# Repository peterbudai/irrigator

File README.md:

# IrriGator

WiFi enabled irrigation control

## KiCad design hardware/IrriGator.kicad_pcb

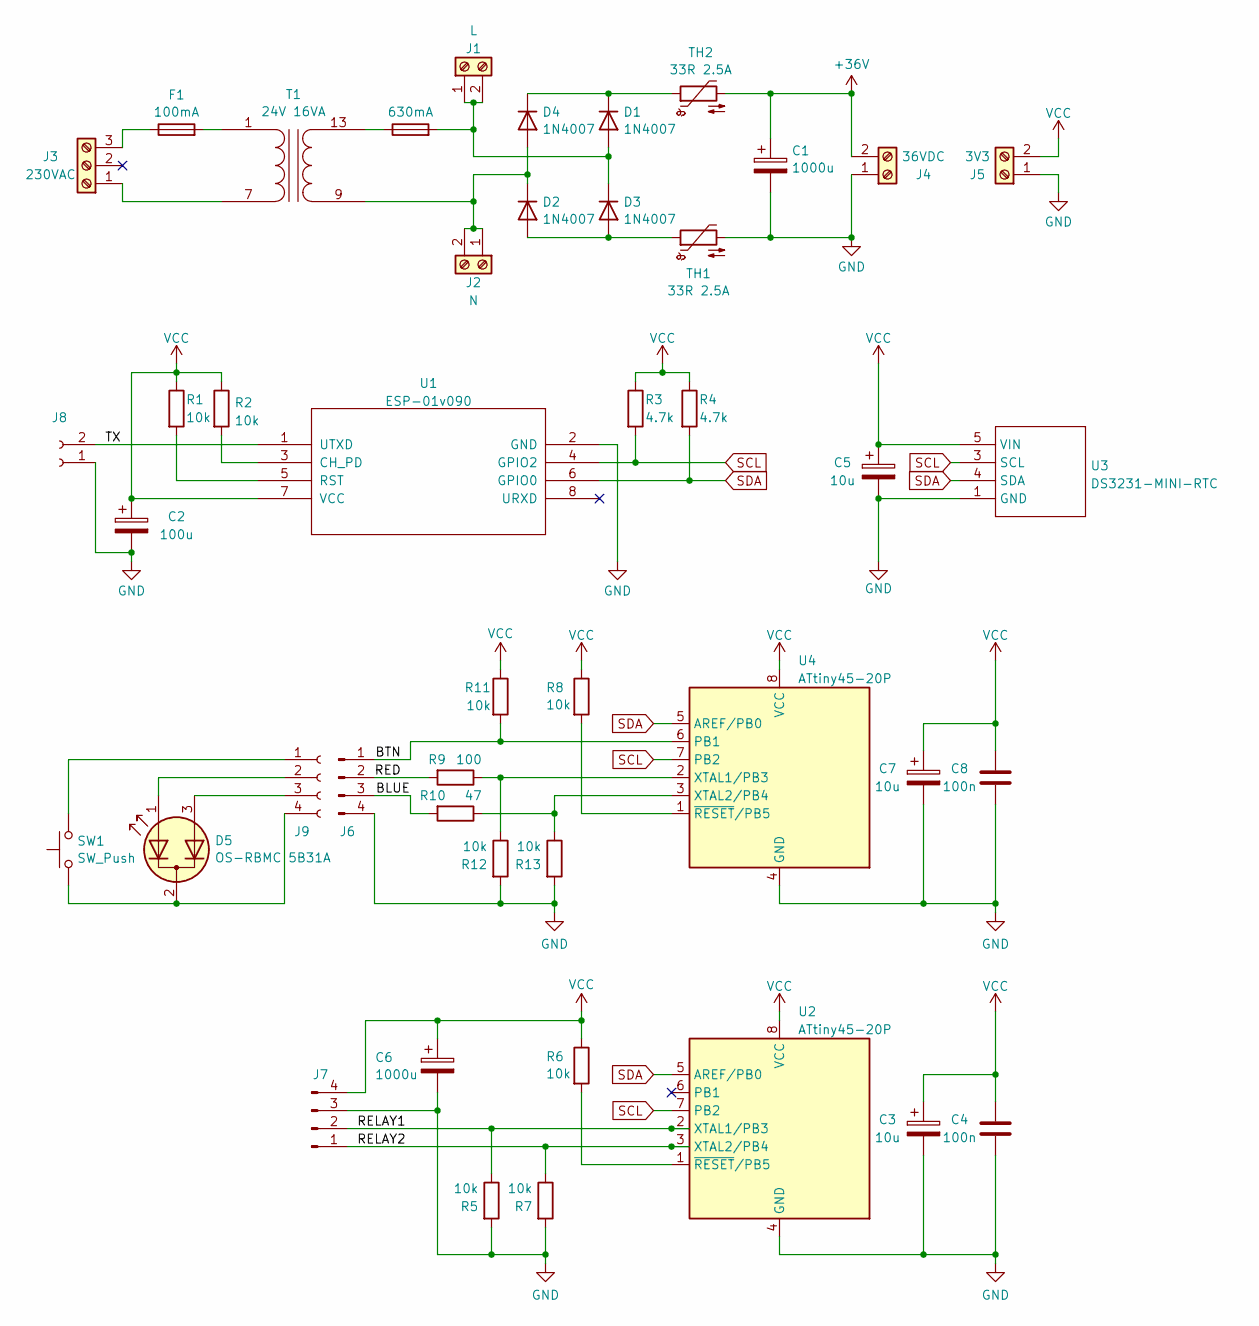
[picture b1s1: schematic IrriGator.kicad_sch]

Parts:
C1: 1000u; CP_Radial_D16.0mm_P7.50mm
C2: 100u; CP_Radial_D5.0mm_P2.50mm
C3, C5, C7: 10u; CP_Radial_D5.0mm_P2.50mm
C4, C8: 100n; C_Disc_D5.0mm_W2.5mm_P2.50mm
C6: 1000u; CP_Radial_D10.0mm_P5.00mm
D1, D2, D3, D4: 1N4007; D_DO-41_SOD81_P10.16mm_Horizontal
D5: OS-RBMC 5B31A; LED_D5.0mm-3
F1: 100mA; Fuseholder_Cylinder-5x20mm_Stelvio-Kontek_PTF78_Horizontal_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
F2: 630mA; Fuseholder_Cylinder-5x20mm_Stelvio-Kontek_PTF78_Horizontal_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
J1: L; TerminalBlock_Phoenix_MKDS-1,5-2-5.08_1x02_P5.08mm_Horizont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
J2: N; TerminalBlock_Phoenix_MKDS-1,5-2-5.08_1x02_P5.08mm_Horizont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
J3: 230VAC; TerminalBlock_Phoenix_MKDS-1,5-3-5.08_1x03_P5.08mm_Horizont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
J4: 36VDC; TerminalBlock_Phoenix_MKDS-1,5-2-5.08_1x02_P5.08mm_Horizont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
J5: 3V3; TerminalBlock_Phoenix_MKDS-1,5-2-5.08_1x02_P5.08mm_Horizont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
J6, J7: Conn_01x04_Pin; PinHeader_1x04_P2.54mm_Vertical
J8: Conn_01x02_Socket; PinSocket_1x02_P2.54mm_Vertical
J9: Conn_01x04_Socket; SolderWire-0.1sqmm_1x04_P3.6mm_D0.4mm_OD1mm
R1, R2, R5, R6, R7, R8, R11, R12, R13: 10k; R_Axial_DIN0204_L3.6mm_D1.6mm_P7.62mm_Horizontal
R3, R4: 4.7k; R_Axial_DIN0204_L3.6mm_D1.6mm_P7.62mm_Horizontal
R9: 100; R_Axial_DIN0204_L3.6mm_D1.6mm_P7.62mm_Horizontal
R10: 47; R_Axial_DIN0204_L3.6mm_D1.6mm_P7.62mm_Horizontal
SW1: SW_Push; SW_PUSH-12mm
T1: 24V 16VA; MYRRA 44306 PCB Transformer 1x24V 16VA 230V
TH1, TH2: 33R 2.5A; RV_Disc_D15.5mm_W6.8mm_P7.5mm
U1: ESP-01v090; ESP-01
U2, U4: ATtiny45-20P; DIP-8_W7.62mm_Socket
U3: DS3231-MINI-RTC

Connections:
+36V: C1.1, J4.2, TH2.2
/BLUE: J6.3, R10.2
/BTN: J6.1, R11.2, U4.6 (PB1)
/RED: J6.2, R9.2
/RELAY1: J7.2, R5.1, U2.2 (XTAL1/PB3)
/RELAY2: J7.1, R7.1, U2.3 (XTAL2/PB4)
/TX: J8.2, U1.1 (UTXD)
GND: C1.2, C2.2, C3.2, C4.1, C5.2, C6.2, C7.2, C8.1, J4.1, J5.1, J6.4, J7.3, J8.1, R5.2, R7.2, R12.2, R13.2, TH1.2, U1.2 (GND), U2.4 (GND), U3.1 (GND), U4.4 (GND)
unnamed: D1.2 (A), D3.1 (K), F2.2, J1.1, J1.2
unnamed: D1.1 (K), D4.1 (K), TH2.1
unnamed: D2.2 (A), D3.2 (A), TH1.1
unnamed: D2.1 (K), D4.2 (A), J2.1, J2.2, T1.9 (SA)
unnamed: D5.1 (A1), J9.2
unnamed: D5.3 (A2), J9.3
unnamed: D5.2 (K), J9.4, SW1.1
unnamed: J3.1, T1.7 (AB)
unnamed: F1.1, J3.3
unnamed: J9.1, SW1.2
unnamed: F1.2, T1.1 (AA)
unnamed: F2.1, T1.13 (SB)
unnamed: R2.2, U1.3 (CH_PD)
unnamed: R1.2, U1.5 (RST)
unnamed: R6.2, U2.1 (~RESET/PB5)
unnamed: R9.1, R12.1, U4.2 (XTAL1/PB3)
unnamed: R10.1, R13.1, U4.3 (XTAL2/PB4)
unnamed: R8.2, U4.1 (~RESET/PB5)
SCL: R3.2, U1.4 (GPIO2), U2.7 (PB2), U3.3 (SCL), U4.7 (PB2)
SDA: R4.2, U1.6 (GPIO0), U2.5 (AREF/PB0), U3.4 (SDA), U4.5 (AREF/PB0)
VCC: C2.1, C3.1, C4.2, C5.1, C6.1, C7.1, C8.2, J5.2, J7.4, R1.1, R2.1, R3.1, R4.1, R6.1, R8.1, R11.1, U1.7 (VCC), U2.8 (VCC), U3.5 (VIN), U4.8 (VCC)

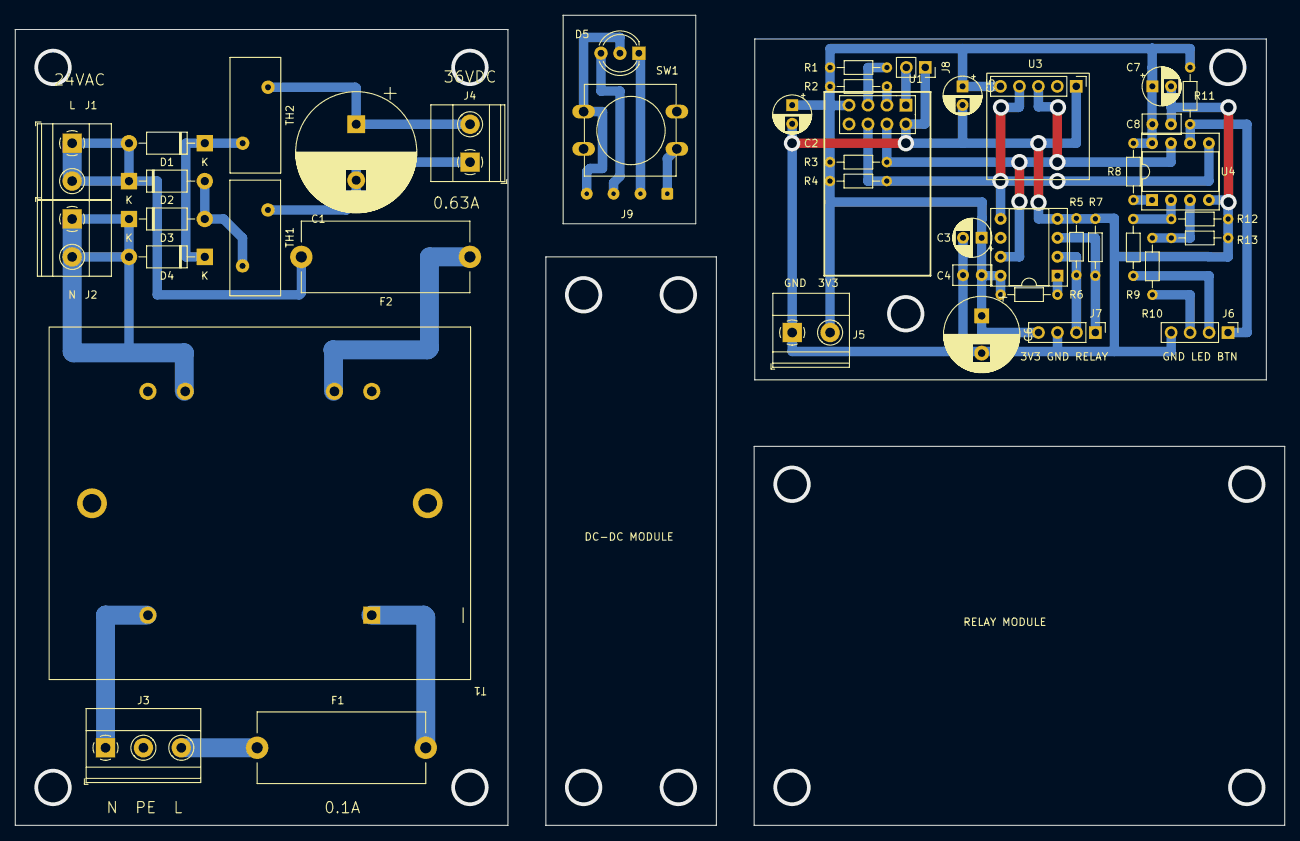
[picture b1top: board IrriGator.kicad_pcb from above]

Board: 2 copper layers, 170.2 x 108.6 mm, 45 parts (0 on the bottom side), 29 nets.

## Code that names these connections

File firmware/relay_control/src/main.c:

#include <stdint.h>
#include <avr/interrupt.h>
#include <avr/sleep.h>
#include <avr/wdt.h>

#include "usiTwiSlave.h"

// ------------------------------------------------------------- 
// Constants
// -------------------------------------------------------------

// This will be the I2C address of this slave controller
#define I2C_ADDR 0x0A

// Command byte constants
#define CMD_MASK 0xF0
#define CMD_OFF 0x10
#define CMD_ON 0x20
#define CMD_SET 0x30

#define RELAY_MASK 0x03
#define RELAY_1 PB3             // Relay 1 is connected to PORTB3
#define RELAY_2 PB4             // Relay 2 is connected to PORTB4

// Handle I2C data sent from master. Accepts a single command byte.
//
// Command byte structure:
// Bit 7 6 5 4 3 2 1 0
//     \--+--/ \+/ | |
//        |     |  | +-- Relay 1 select/state
//        |     |  +---- Relay 2 select/state
//        |     +------- Unused (ignored, should be 0)
//        +------------- Command
static void onReceive(uint8_t amount) {
    while(amount--) {
        // Read next command byte from I2C input buffer
        uint8_t command = usiTwiReceiveByte();

        // Execute command
        switch(command & CMD_MASK) {
            case CMD_OFF:
                // Turn the specified relays off
                PORTB &= ~((command & RELAY_MASK) << RELAY_1);
                break;
            case CMD_ON:
                // Turn the specified relays on
                PORTB |= (command & RELAY_MASK) << RELAY_1;
                break;
            case CMD_SET:
                // Set the relays to the specified state (on: 1, off: 0)
                PORTB = (PORTB & ~(_BV(RELAY_2) | _BV(RELAY_1))) | ((command & RELAY_MASK) << RELAY_1);
                break;
            default:
                // Unknown or ping command, do nothing
                break;
        }
    }
    wdt_reset();
}

// Handle I2C data read by master. Returns relay status in a single byte.
//
// Status byte structure:
// Bit 7 6 5 4 3 2 1 0
//     \----+----/ | |
//          |      | +-- Relay 1 state (on: 1, off: 0)
//          |      +---- Relay 2 state (on: 1, off: 0)
//          +----------- Unused (set to 0)
static void onRequest(void) {
    uint8_t state = (PORTB & (_BV(RELAY_2) | _BV(RELAY_1))) >> RELAY_1;
    usiTwiTransmitByte(state);
    wdt_reset();
}

// Main function
int main(void) {
    // -------------------------------------------------------------
    // Init all peripherials
    // -------------------------------------------------------------

    // Relay control ports PB3 and PB4 as outputs (initially LOW)
    DDRB |= _BV(RELAY_2) | _BV(RELAY_1);
    PORTB &= ~(_BV(RELAY_2) | _BV(RELAY_1));

    // I2C inputs on pins PB2 and PB0
    usiTwiSlaveInit(I2C_ADDR, onReceive, onRequest);

    // Unused pin PB1 as input with internal pull-up enabled
    DDRB &= ~_BV(PB1);
    PORTB |= _BV(PB1);

    // -------------------------------------------------------------
    // Main loop - wait for external events and handle them
    // -------------------------------------------------------------
    
    // Enable sleep and interrupts
    set_sleep_mode(SLEEP_MODE_IDLE);
    sleep_enable();
    sei();

    // Reset if no I2C command received for 8 seconds
    // Safety measure: if I2C master or bus hangs, better turn off relays and reinit
    wdt_enable(WDTO_8S);
    for (;;) {
        sleep_cpu();
    }
}

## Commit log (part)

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2024-05-06 Uploaded logo
2024-05-06 Made logo transparent and look smaller.
2024-05-06 Play with logo
2024-05-06 Add initial version of hardware
2024-05-06 Added initial formware code for relay controller
2024-05-06 Add initial code for the main controller
2024-05-06 Added comments, timer init and removed warnings
2024-05-06 Added initial code for the user interface controller
2024-05-06 Added code comments, fix compiler warning
2024-05-06 Added pushbutton sensing and debouncing.
2024-05-06 Updated PCB layout to better match the actual build
2024-05-06 Moved rectifier part to the transformer module, DC-DC stepdown becomes an external module
2024-05-06 Make watchdog reset more conservative
2024-05-06 Simplified AVR source code structure
2024-05-07 Added test code for user controller
2024-05-11 Added UART debug pins to the hardware
2024-05-11 Added RTC, Blynk and Wifi libraries to the main controller
2024-05-11 Start working on main controller logic
2024-05-12 Added cloud syncing to clock properties
2024-05-16 Updated I2C slave code to a new version. This should be able to handle sole writes and reads.
2024-05-17 Improved debug output.
2024-05-17 Fix compiler errors
2024-05-17 Change I2C communication to write&read cycles to avoid blocking I2C state machine in slaves.
2024-05-20 Implement irrigation schedule logic
2024-06-08 WiFi settings fixes and state logic fix
2024-06-08 Switch to ESP32-WROOM-32U-128MBit
2026-04-27 Moved to ESPHome implementation
2026-04-27 Added custom component to display system status via I2C
